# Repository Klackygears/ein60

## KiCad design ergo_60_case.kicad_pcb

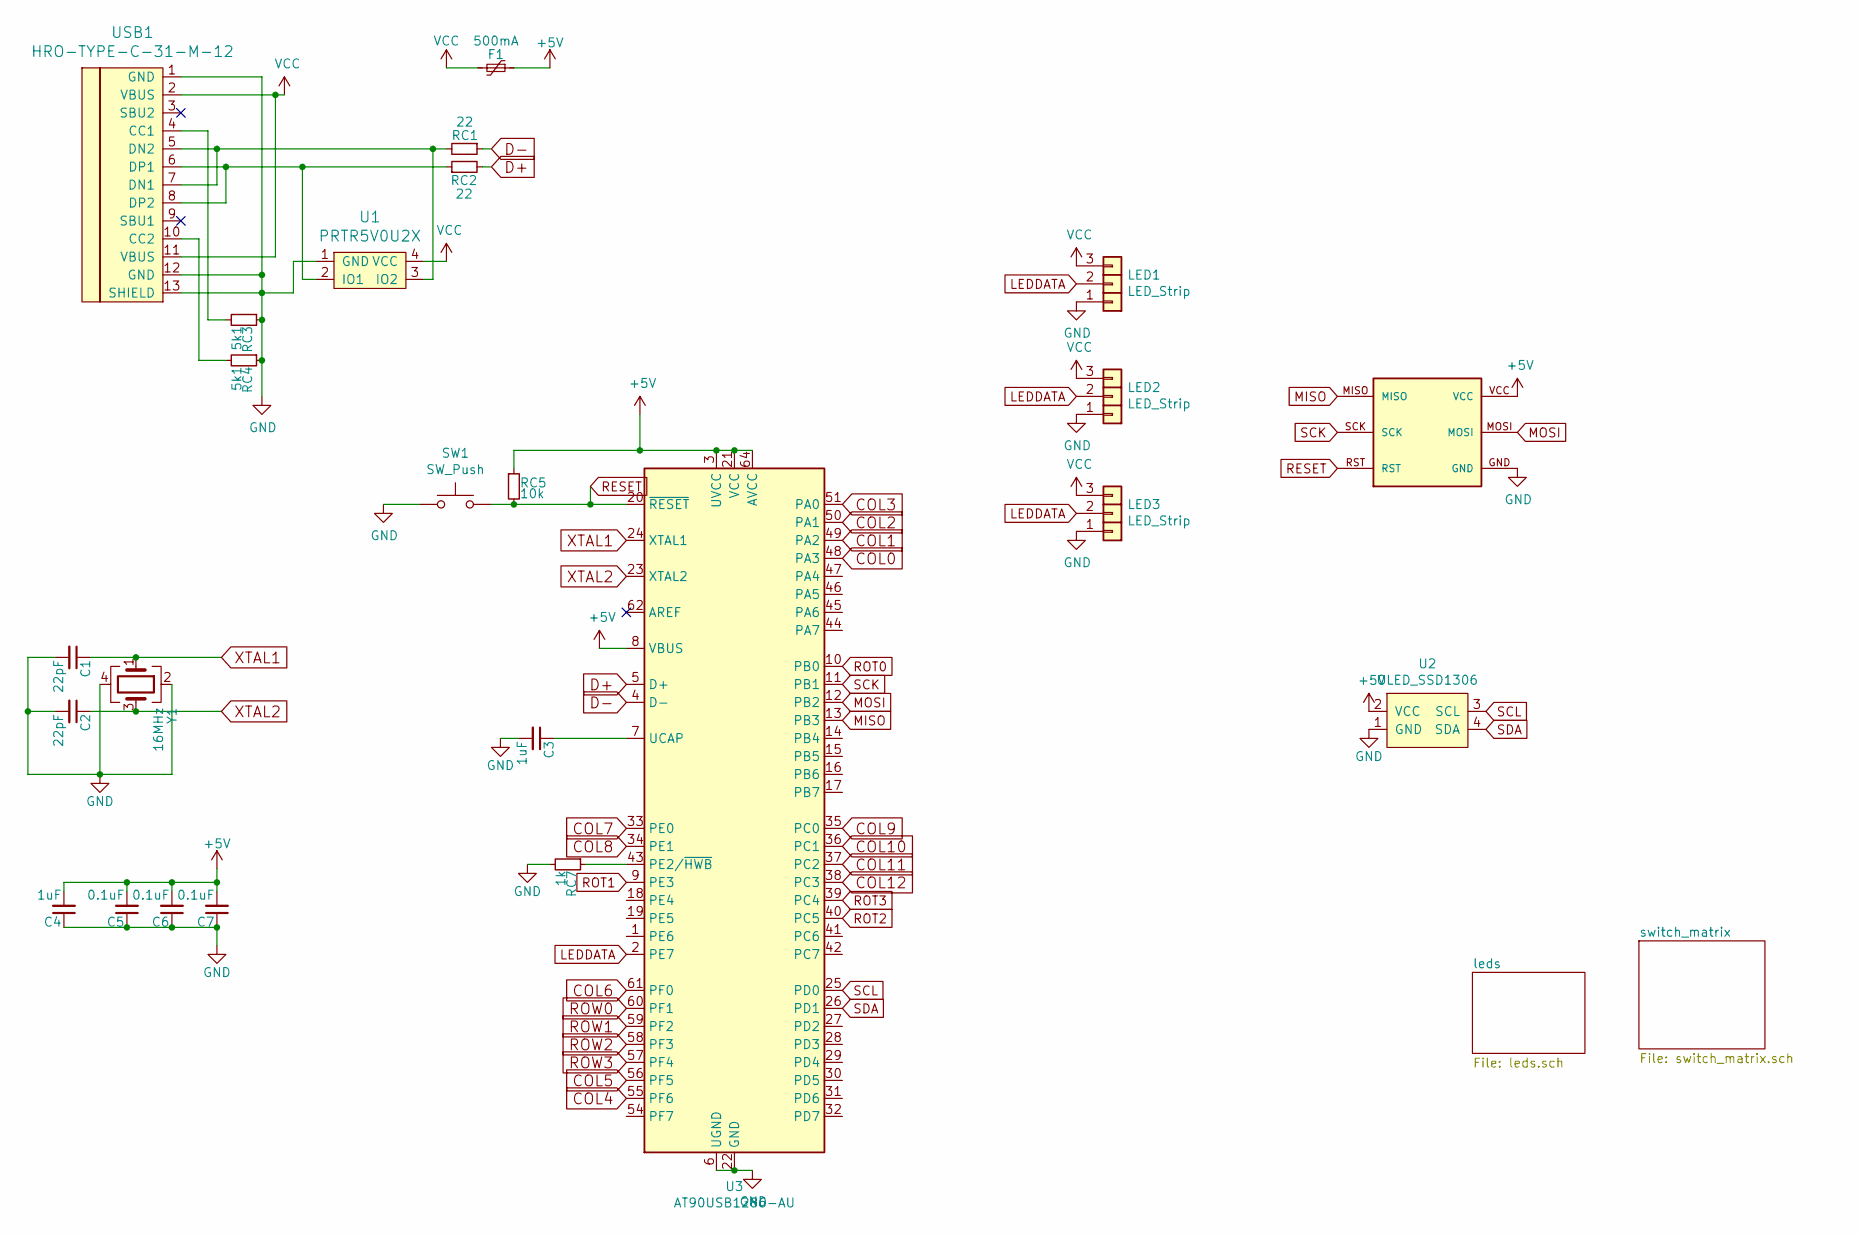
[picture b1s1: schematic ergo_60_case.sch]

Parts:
C1, C2: 22pF; C_0603_1608Metric
C3, C4: 1uF; C_0603_1608Metric
C5, C6, C7: 0.1uF; C_0603_1608Metric
F1: 500mA; Fuse_1206_3216Metric
LED1, LED3: LED_Strip; StripLED
LED2: LED_Strip; StripLED_BackOnly
RC1, RC2: 22; R_0603_1608Metric
RC3, RC4: 5k1; R_0603_1608Metric
RC5: 10k; R_0603_1608Metric
RC7: 1k; R_0603_1608Metric
SW1: SW_Push; SW_PTS636_SM43J_SMTR_LFS
U1: PRTR5V0U2X; Nexperia-SOT143B-01_2017-0-MFG_PRTR5V0U2X
U2: OLED_SSD1306; SSD1306_128x64OLED_wHoles
U3: AT90USB1286-AU; AT90USB1286-AU_QFP80P1600X1600X120-64N
U4: AVR-ISP; AVR-ISP_header
USB1: HRO-TYPE-C-31-M-12; HRO-TYPE-C-31-M-12-Assembly
Y1: 16MHz; Crystal_SMD_3225-4Pin_3.2x2.5mm

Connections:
+5V: C4.2, C5.2, C6.2, C7.2, F1.1, RC5.1, U2.2 (VCC), U3.3 (UVCC), U3.8 (VBUS), U3.21 (VCC), U3.52 (VCC), U3.64 (AVCC), U4.VCC
COL0: U3.48 (PA3); also elsewhere on the board
COL1: U3.49 (PA2); also elsewhere on the board
COL2: U3.50 (PA1); also elsewhere on the board
COL3: U3.51 (PA0); also elsewhere on the board
COL4: U3.55 (PF6); also elsewhere on the board
COL5: U3.56 (PF5); also elsewhere on the board
COL6: U3.61 (PF0); also elsewhere on the board
COL7: U3.33 (PE0); also elsewhere on the board
COL8: U3.34 (PE1); also elsewhere on the board
COL9: U3.35 (PC0); also elsewhere on the board
COL10: U3.36 (PC1); also elsewhere on the board
COL11: U3.37 (PC2); also elsewhere on the board
COL12: U3.38 (PC3); also elsewhere on the board
D+: RC2.2, U3.5 (D+)
D-: RC1.1, U3.4 (D-)
GND: C1.2, C2.2, C3.2, C4.1, C5.1, C6.1, C7.1, LED1.1, LED2.1, LED3.1, RC3.1, RC4.1, RC7.2, SW1.1, U1.1 (GND), U2.1 (GND), U3.6 (UGND), U3.22 (GND), U3.53 (GND), U3.63 (GND), U4.GND, USB1.1 (GND), USB1.12 (GND), USB1.13 (SHIELD), Y1.2, Y1.4; also elsewhere on the board
LEDDATA: LED1.2, LED2.2, LED3.2, U3.2 (PE7); also elsewhere on the board
MISO: U3.13 (PB3), U4.MISO
MOSI: U3.12 (PB2), U4.MOSI
unnamed: C3.1, U3.7 (UCAP)
unnamed: RC1.2, U1.3 (IO2), USB1.5 (DN2), USB1.7 (DN1)
unnamed: RC2.1, U1.2 (IO1), USB1.6 (DP1), USB1.8 (DP2)
unnamed: RC3.2, USB1.4 (CC1)
unnamed: RC4.2, USB1.10 (CC2)
unnamed: RC7.1, U3.43 (PE2/~HWB)
RESET: RC5.2, SW1.2, U3.20 (~RESET), U4.RST
ROT0: U3.10 (PB0); also elsewhere on the board
ROT1: U3.9 (PE3); also elsewhere on the board
ROT2: U3.40 (PC5); also elsewhere on the board
ROT3: U3.39 (PC4); also elsewhere on the board
ROW0: U3.60 (PF1); also elsewhere on the board
ROW1: U3.59 (PF2); also elsewhere on the board
ROW2: U3.58 (PF3); also elsewhere on the board
ROW3: U3.57 (PF4); also elsewhere on the board
SCK: U3.11 (PB1), U4.SCK
SCL: U2.3 (SCL), U3.25 (PD0)
SDA: U2.4 (SDA), U3.26 (PD1)
VCC: F1.2, LED1.3, LED2.3, LED3.3, U1.4 (VCC), USB1.2 (VBUS), USB1.11 (VBUS); also elsewhere on the board
XTAL1: C1.1, U3.24 (XTAL1), Y1.1
XTAL2: C2.1, U3.23 (XTAL2), Y1.3

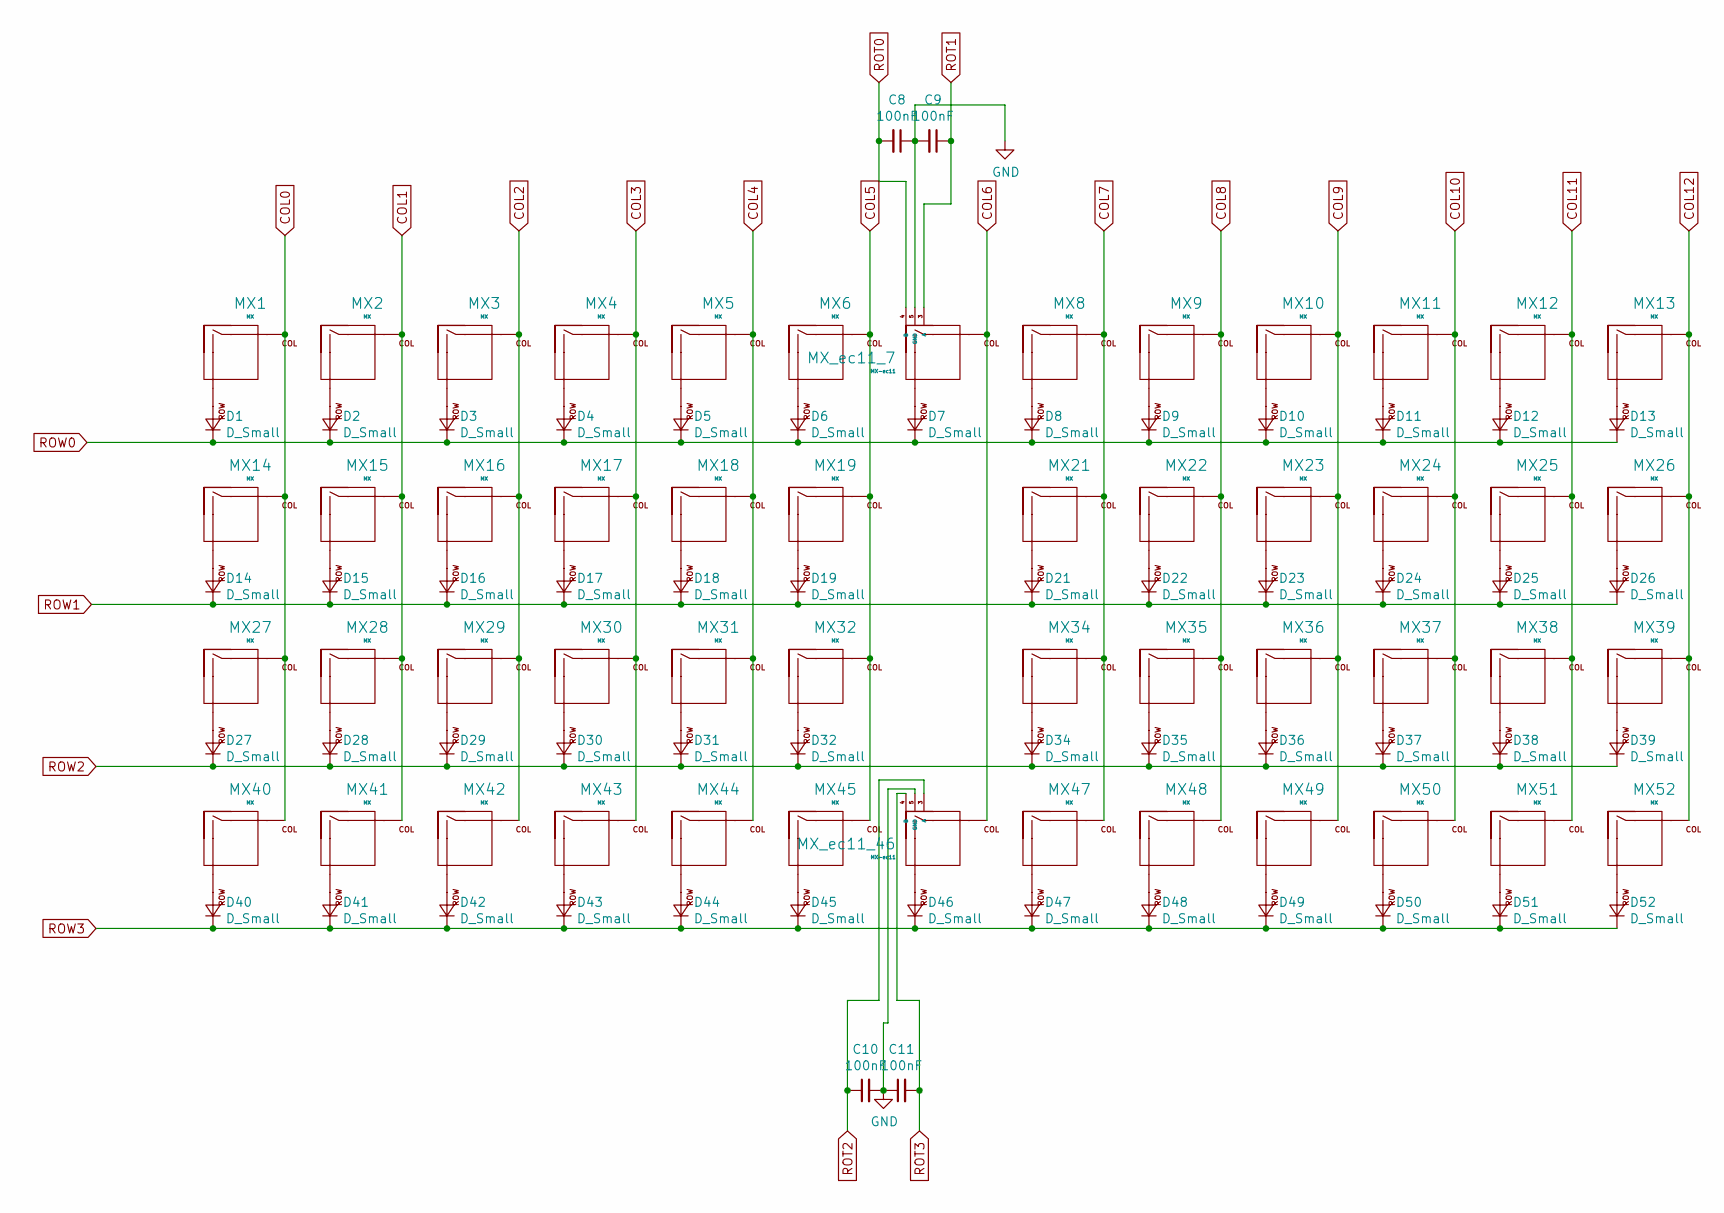
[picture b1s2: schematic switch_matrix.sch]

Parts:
C8, C9, C10, C11: 100nF; C_0603_1608Metric
D1, D2, D3, D4, D5, D6, D7, D8, D9, D10, D11, D12, D13, D14, D15, D16, D17, D18, D19, D21, D22, D23, D24, D25, D26, D27, D28, D29, D30, D31, D32, D34, D35, D36, D37, D38, D39, D40, D41, D42, D43, D44, D45, D46, D47, D48, D49, D50, D51, D52: D_Small; D_SOD-123
MX1, MX2, MX3, MX4, MX5, MX6, MX8, MX9, MX10, MX11, MX12, MX13, MX14, MX15, MX16, MX17, MX18, MX19, MX21, MX22, MX23, MX24, MX25, MX26, MX27, MX28, MX29, MX30, MX31, MX32, MX34, MX35, MX36, MX37, MX38, MX39, MX40, MX41, MX42, MX43, MX44, MX45, MX47, MX48, MX49, MX50, MX51, MX52: MX; MX-1U-Hotswap-Antishear
MX_ec11_7, MX_ec11_46: MX-ec11; MX-1U-Hotswap-Antishear-ec11

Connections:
COL0: MX1.1 (COL), MX14.1 (COL), MX27.1 (COL), MX40.1 (COL); also elsewhere on the board
COL1: MX2.1 (COL), MX15.1 (COL), MX28.1 (COL), MX41.1 (COL); also elsewhere on the board
COL2: MX3.1 (COL), MX16.1 (COL), MX29.1 (COL), MX42.1 (COL); also elsewhere on the board
COL3: MX4.1 (COL), MX17.1 (COL), MX30.1 (COL), MX43.1 (COL); also elsewhere on the board
COL4: MX5.1 (COL), MX18.1 (COL), MX31.1 (COL), MX44.1 (COL); also elsewhere on the board
COL5: MX6.1 (COL), MX19.1 (COL), MX32.1 (COL), MX45.1 (COL); also elsewhere on the board
COL6: MX_ec11_7.1 (COL), MX_ec11_46.1 (COL); also elsewhere on the board
COL7: MX8.1 (COL), MX21.1 (COL), MX34.1 (COL), MX47.1 (COL); also elsewhere on the board
COL8: MX9.1 (COL), MX22.1 (COL), MX35.1 (COL), MX48.1 (COL); also elsewhere on the board
COL9: MX10.1 (COL), MX23.1 (COL), MX36.1 (COL), MX49.1 (COL); also elsewhere on the board
COL10: MX11.1 (COL), MX24.1 (COL), MX37.1 (COL), MX50.1 (COL); also elsewhere on the board
COL11: MX12.1 (COL), MX25.1 (COL), MX38.1 (COL), MX51.1 (COL); also elsewhere on the board
COL12: MX13.1 (COL), MX26.1 (COL), MX39.1 (COL), MX52.1 (COL); also elsewhere on the board
GND: C8.1, C9.2, C10.2, C11.1, MX_ec11_7.5 (GND), MX_ec11_46.5 (GND); also elsewhere on the board
unnamed: D1.2 (A), MX1.2 (ROW)
unnamed: D2.2 (A), MX2.2 (ROW)
unnamed: D3.2 (A), MX3.2 (ROW)
unnamed: D4.2 (A), MX4.2 (ROW)
unnamed: D5.2 (A), MX5.2 (ROW)
unnamed: D6.2 (A), MX6.2 (ROW)
unnamed: D7.2 (A), MX_ec11_7.2 (ROW)
unnamed: D8.2 (A), MX8.2 (ROW)
unnamed: D9.2 (A), MX9.2 (ROW)
unnamed: D10.2 (A), MX10.2 (ROW)
unnamed: D11.2 (A), MX11.2 (ROW)
unnamed: D12.2 (A), MX12.2 (ROW)
unnamed: D13.2 (A), MX13.2 (ROW)
unnamed: D14.2 (A), MX14.2 (ROW)
unnamed: D15.2 (A), MX15.2 (ROW)
unnamed: D16.2 (A), MX16.2 (ROW)
unnamed: D17.2 (A), MX17.2 (ROW)
unnamed: D18.2 (A), MX18.2 (ROW)
unnamed: D19.2 (A), MX19.2 (ROW)
unnamed: D21.2 (A), MX21.2 (ROW)
unnamed: D22.2 (A), MX22.2 (ROW)
unnamed: D23.2 (A), MX23.2 (ROW)
unnamed: D24.2 (A), MX24.2 (ROW)
unnamed: D25.2 (A), MX25.2 (ROW)
unnamed: D26.2 (A), MX26.2 (ROW)
unnamed: D27.2 (A), MX27.2 (ROW)
unnamed: D28.2 (A), MX28.2 (ROW)
unnamed: D29.2 (A), MX29.2 (ROW)
unnamed: D30.2 (A), MX30.2 (ROW)
unnamed: D31.2 (A), MX31.2 (ROW)
unnamed: D32.2 (A), MX32.2 (ROW)
unnamed: D34.2 (A), MX34.2 (ROW)
unnamed: D35.2 (A), MX35.2 (ROW)
unnamed: D36.2 (A), MX36.2 (ROW)
unnamed: D37.2 (A), MX37.2 (ROW)
unnamed: D38.2 (A), MX38.2 (ROW)
unnamed: D39.2 (A), MX39.2 (ROW)
unnamed: D40.2 (A), MX40.2 (ROW)
unnamed: D41.2 (A), MX41.2 (ROW)
unnamed: D42.2 (A), MX42.2 (ROW)
unnamed: D43.2 (A), MX43.2 (ROW)
unnamed: D44.2 (A), MX44.2 (ROW)
unnamed: D45.2 (A), MX45.2 (ROW)
unnamed: D46.2 (A), MX_ec11_46.2 (ROW)
unnamed: D47.2 (A), MX47.2 (ROW)
unnamed: D48.2 (A), MX48.2 (ROW)
unnamed: D49.2 (A), MX49.2 (ROW)
unnamed: D50.2 (A), MX50.2 (ROW)
unnamed: D51.2 (A), MX51.2 (ROW)
unnamed: D52.2 (A), MX52.2 (ROW)
ROT0: C8.2, MX_ec11_7.4 (B); also elsewhere on the board
ROT1: C9.1, MX_ec11_7.3 (A); also elsewhere on the board
ROT2: C10.1, MX_ec11_46.3 (A); also elsewhere on the board
ROT3: C11.2, MX_ec11_46.4 (B); also elsewhere on the board
ROW0: D1.1 (K), D2.1 (K), D3.1 (K), D4.1 (K), D5.1 (K), D6.1 (K), D7.1 (K), D8.1 (K), D9.1 (K), D10.1 (K), D11.1 (K), D12.1 (K), D13.1 (K); also elsewhere on the board
ROW1: D14.1 (K), D15.1 (K), D16.1 (K), D17.1 (K), D18.1 (K), D19.1 (K), D21.1 (K), D22.1 (K), D23.1 (K), D24.1 (K), D25.1 (K), D26.1 (K); also elsewhere on the board
ROW2: D27.1 (K), D28.1 (K), D29.1 (K), D30.1 (K), D31.1 (K), D32.1 (K), D34.1 (K), D35.1 (K), D36.1 (K), D37.1 (K), D38.1 (K), D39.1 (K); also elsewhere on the board
ROW3: D40.1 (K), D41.1 (K), D42.1 (K), D43.1 (K), D44.1 (K), D45.1 (K), D46.1 (K), D47.1 (K), D48.1 (K), D49.1 (K), D50.1 (K), D51.1 (K), D52.1 (K); also elsewhere on the board

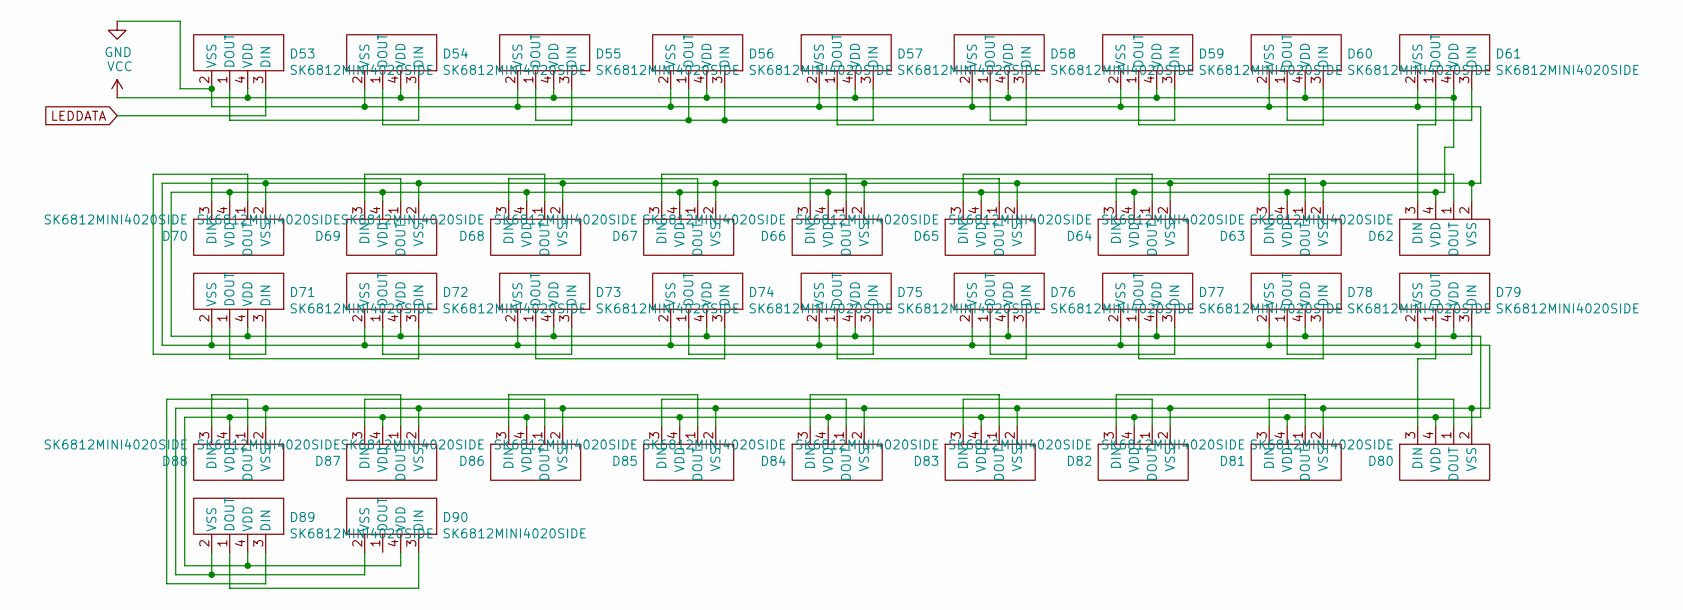
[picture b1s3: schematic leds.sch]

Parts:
D53, D54, D55, D56, D57, D58, D59, D60, D61, D62, D63, D64, D65, D66, D67, D68, D69, D70, D71, D72, D73, D74, D75, D76, D77, D78, D79, D80, D81, D82, D83, D84, D85, D86, D87, D88, D89, D90: SK6812MINI4020SIDE; SK6812_SIDE-A

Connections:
GND: D53.2 (VSS), D54.2 (VSS), D55.2 (VSS), D56.2 (VSS), D57.2 (VSS), D58.2 (VSS), D59.2 (VSS), D60.2 (VSS), D61.2 (VSS), D62.2 (VSS), D63.2 (VSS), D64.2 (VSS), D65.2 (VSS), D66.2 (VSS), D67.2 (VSS), D68.2 (VSS), D69.2 (VSS), D70.2 (VSS), D71.2 (VSS), D72.2 (VSS), D73.2 (VSS), D74.2 (VSS), D75.2 (VSS), D76.2 (VSS), D77.2 (VSS), D78.2 (VSS), D79.2 (VSS), D80.2 (VSS), D81.2 (VSS), D82.2 (VSS), D83.2 (VSS), D84.2 (VSS), D85.2 (VSS), D86.2 (VSS), D87.2 (VSS), D88.2 (VSS), D89.2 (VSS), D90.2 (VSS); also elsewhere on the board
LEDDATA: D53.3 (DIN); also elsewhere on the board
unnamed: D53.1 (DOUT), D54.3 (DIN)
unnamed: D54.1 (DOUT), D55.3 (DIN)
unnamed: D57.1 (DOUT), D58.3 (DIN)
unnamed: D58.1 (DOUT), D59.3 (DIN)
unnamed: D59.1 (DOUT), D60.3 (DIN)
unnamed: D60.1 (DOUT), D61.3 (DIN)
unnamed: D61.1 (DOUT), D62.3 (DIN)
unnamed: D62.1 (DOUT), D63.3 (DIN)
unnamed: D63.1 (DOUT), D64.3 (DIN)
unnamed: D64.1 (DOUT), D65.3 (DIN)
unnamed: D65.1 (DOUT), D66.3 (DIN)
unnamed: D66.1 (DOUT), D67.3 (DIN)
unnamed: D67.1 (DOUT), D68.3 (DIN)
unnamed: D68.1 (DOUT), D69.3 (DIN)
unnamed: D69.1 (DOUT), D70.3 (DIN)
unnamed: D70.1 (DOUT), D71.3 (DIN)
unnamed: D71.1 (DOUT), D72.3 (DIN)
unnamed: D72.1 (DOUT), D73.3 (DIN)
unnamed: D73.1 (DOUT), D74.3 (DIN)
unnamed: D74.1 (DOUT), D75.3 (DIN)
unnamed: D75.1 (DOUT), D76.3 (DIN)
unnamed: D76.1 (DOUT), D77.3 (DIN)
unnamed: D77.1 (DOUT), D78.3 (DIN)
unnamed: D78.1 (DOUT), D79.3 (DIN)
unnamed: D79.1 (DOUT), D80.3 (DIN)
unnamed: D80.1 (DOUT), D81.3 (DIN)
unnamed: D81.1 (DOUT), D82.3 (DIN)
unnamed: D82.1 (DOUT), D83.3 (DIN)
unnamed: D83.1 (DOUT), D84.3 (DIN)
unnamed: D84.1 (DOUT), D85.3 (DIN)
unnamed: D85.1 (DOUT), D86.3 (DIN)
unnamed: D86.1 (DOUT), D87.3 (DIN)
unnamed: D87.1 (DOUT), D88.3 (DIN)
unnamed: D88.1 (DOUT), D89.3 (DIN)
unnamed: D89.1 (DOUT), D90.3 (DIN)
VCC: D53.4 (VDD), D54.4 (VDD), D55.4 (VDD), D56.4 (VDD), D57.4 (VDD), D58.4 (VDD), D59.4 (VDD), D60.4 (VDD), D61.4 (VDD), D62.4 (VDD), D63.4 (VDD), D64.4 (VDD), D65.4 (VDD), D66.4 (VDD), D67.4 (VDD), D68.4 (VDD), D69.4 (VDD), D70.4 (VDD), D71.4 (VDD), D72.4 (VDD), D73.4 (VDD), D74.4 (VDD), D75.4 (VDD), D76.4 (VDD), D77.4 (VDD), D78.4 (VDD), D79.4 (VDD), D80.4 (VDD), D81.4 (VDD), D82.4 (VDD), D83.4 (VDD), D84.4 (VDD), D85.4 (VDD), D86.4 (VDD), D87.4 (VDD), D88.4 (VDD), D89.4 (VDD), D90.4 (VDD); also elsewhere on the board

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
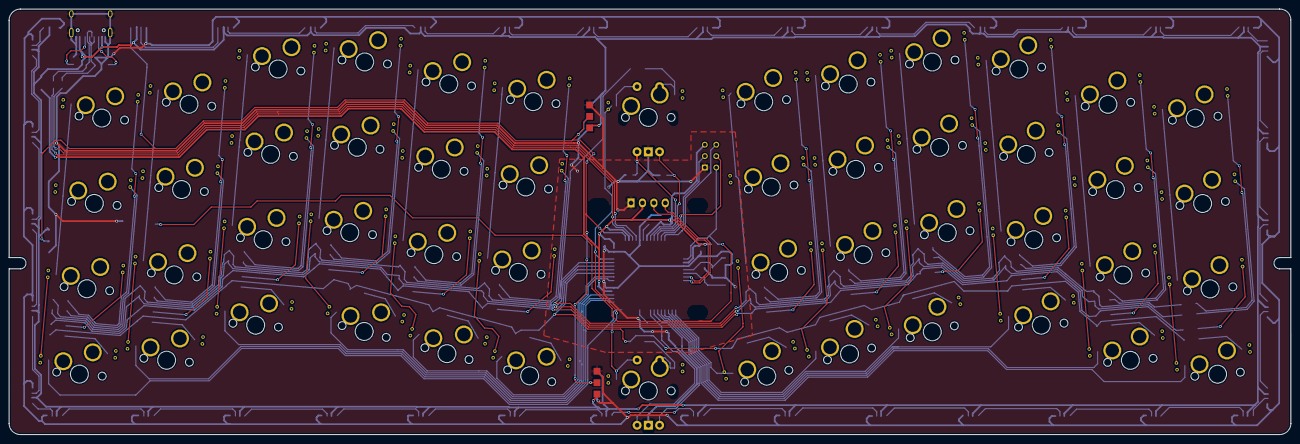
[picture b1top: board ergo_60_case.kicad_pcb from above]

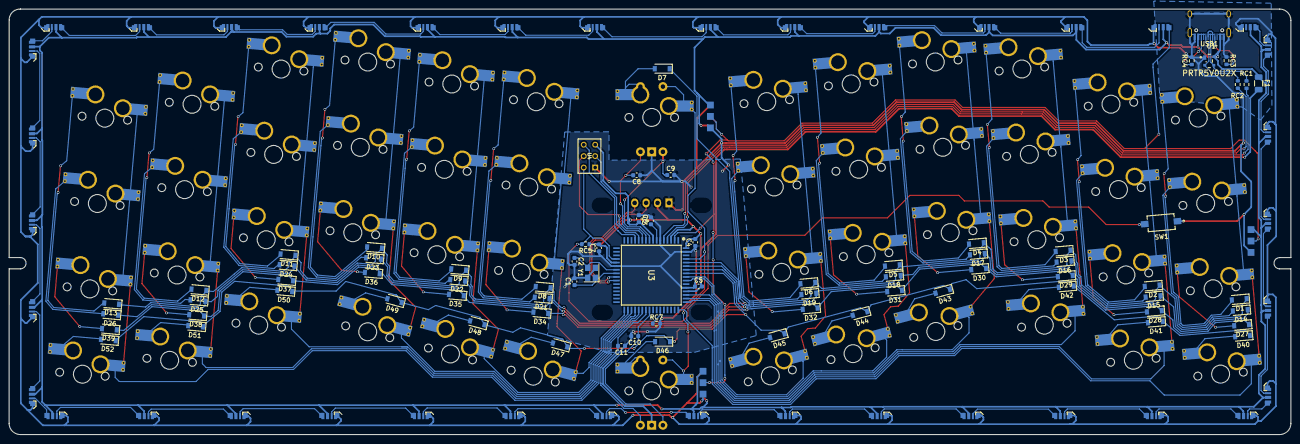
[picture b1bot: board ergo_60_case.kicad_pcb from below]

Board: 2 copper layers, 285.0 x 94.6 mm, 166 parts (74 on the bottom side), 128 nets.

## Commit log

2021-01-21 add files
2021-01-21 update diode spacing
2021-01-24 correcting capacitors
2021-01-25 corrected mising +5v trace and funky looking schematic on led 56
2021-01-31 updates for prod
2021-02-21 correct mcu processor footprint
2021-02-21 smooth routing?
2021-02-22 making more clearance
2021-02-22 progress
2021-02-23 updating footprints for proper clearance
2021-03-15 corrections found during production
2021-03-15 reset switch footprint correction
2021-03-17 Revert "reset switch footprint correction"
    This reverts commit f5c33ba12f206e91247782776fd24d7bcd64934f.
2021-03-17 Revert "corrections found during production"
    This reverts commit 281239c74a6b2efefd07659e333975e0a7958f5f.
2021-03-17 Revert "Revert "corrections found during production""
    This reverts commit 335f6b2a490190a88b35b050fb77acb50b08c7f4.
2021-03-17 Revert "Revert "reset switch footprint correction""
    This reverts commit 81e907175ec75a46385aedb48e9c2c01624081a1.
